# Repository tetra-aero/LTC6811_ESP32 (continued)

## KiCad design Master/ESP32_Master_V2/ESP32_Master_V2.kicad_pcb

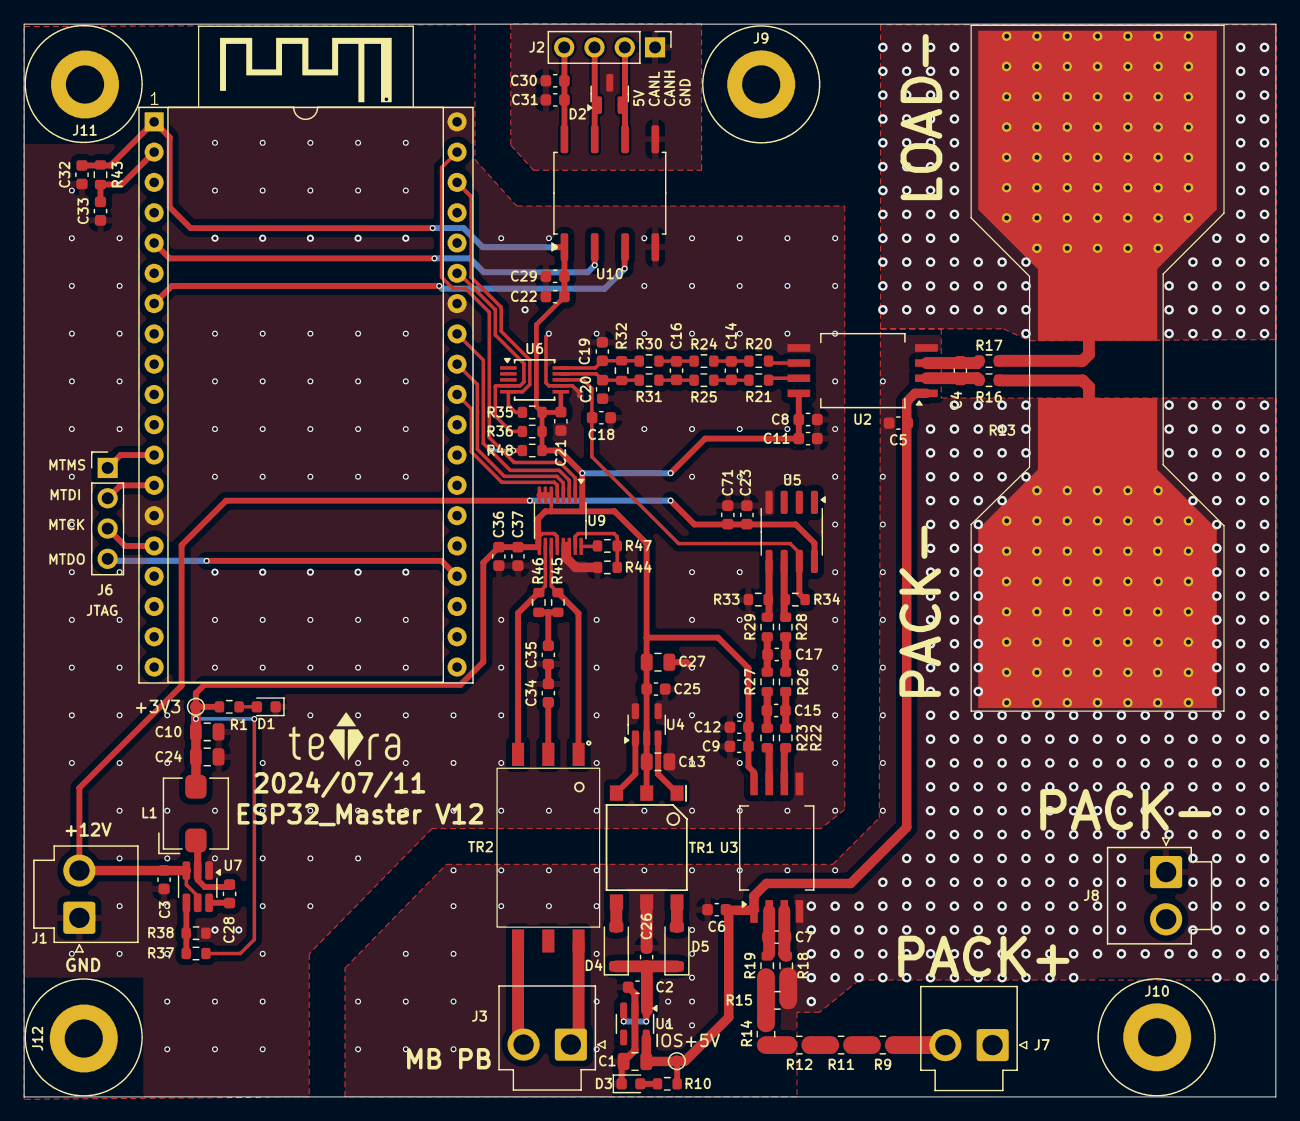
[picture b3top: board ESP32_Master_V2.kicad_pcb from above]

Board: 2 copper layers, 104.9 x 90.0 mm, 106 parts (0 on the bottom side), 67 nets.

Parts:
C1, C10, C13, C24, C27: 10uF/16V; C_0805_2012Metric
C2, C5, C6, C8, C9, C18, C19, C20, C21, C23, C25, C28, C29, C31, C32, C33, C37: 100nF/100V; C_0603_1608Metric
C3, C11, C12: 2.2uF/25V; C_0603_1608Metric
C4, C7: 330pF/100V; C_0603_1608Metric
C14, C15: 2.2nF/16V; C_0603_1608Metric
C16, C17: 220pF/50V; C_0603_1608Metric
C22, C30, C36, C71: 1uF/25V; C_0603_1608Metric
C26: 4.7uF/16V; C_0603_1608Metric
C34, C35: 10nF/100V; C_0603_1608Metric
D1, D3: LED Red; LED_0603_1608Metric
D2: ESD24VS2U; SOT-23
D4, D5: MBR0520; D_SOD-123
J1: PB MB; JST_VH_B2P-VH-B_1x02_P3.96mm_Vertical
J2: CAN; PinHeader_1x04_P2.54mm_Vertical
J3: PA MA; JST_VH_B2P-VH-B_1x02_P3.96mm_Vertical
J6: JTAG /NC; PinHeader_1x04_P2.54mm_Vertical
J7, J8: Check_Votage; JST_VH_B2P-VH-B_1x02_P3.96mm_Vertical
J9, J10, J11, J12: Hole /NC; MountingHole_3.2mm_M3_ISO7380_Pad
L1: 3.3uH; L_Bourns_SRP5030T
LOGO1: teTra /NC; teTra-LOGO
R1, R10: 470R; R_0603_1608Metric
R9, R11, R12, R14: 470KΩ ±0.1% 250mW; R_0805_2012Metric
R13: 0.1MR 1% 15W; R_PSR500HTQFB0L10_Metric_Pad5.2x8.75mm_Hole
R15: 1KΩ ±0.1% 250mW; R_0805_2012Metric
R16, R17, R18, R24, R25, R26, R27, R32: 1K; R_0603_1608Metric
R19: 10R; R_0603_1608Metric
R20, R21, R22, R23: 100R; R_0603_1608Metric
R28, R29: 5.6K; R_0603_1608Metric
R30, R31: 3.3K; R_0603_1608Metric
R33, R34: 33K; R_0603_1608Metric
R35, R36: 4.7K; R_0603_1608Metric
R37: 100K; R_0603_1608Metric
R38: 22.1K; R_0603_1608Metric
R43: 10K; R_0603_1608Metric
R44: 806R; R_0603_1608Metric
R45, R46: 51R; R_0603_1608Metric
R47: 1.2K; R_0603_1608Metric
R48: 2K; R_0603_1608Metric
TP1: IOS+5V; TestPoint_Pad_D1.0mm
TP2: +3V3; TestPoint_Pad_D1.0mm
TR1: Transformer; WURTH-760390015
TR2: HM2108NL
U1: TPS76350; SOT-23-5
U2: AMC1301 or AMC1302; SSO-8_6.8x5.9mm_P1.27mm_Clearance8mm
U3: AMC1301; SSO-8_6.8x5.9mm_P1.27mm_Clearance8mm
U4: SN6501DBV; SOT-23-5
U5: OPA2197IDR; SOIC-8_3.9x4.9mm_P1.27mm
U6: ISL28022; MSOP-10_3x3mm_P0.5mm
U7: LMR51420XDDCR; SOT-23-6_Handsoldering
U8: ESP32-DevKitC V4; ESP32-DevKitc V4_DIP-38_27.9mm×48.2mm
U9: LTC6820; MSOP-16_3x4mm_P0.5mm
U10: ISO1050DUBR; SOP-8_6.62x9.15mm_P2.54mm

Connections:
+3V3: C8.1, C9.1, C10.1, C11.1, C12.1, C13.1, C21.2, C22.1, C24.1, C25.1, C27.1, C29.1, C32.2, C36.2, C37.1, L1.2, R1.2, R35.1, R36.1, R37.2, R43.1, R48.1, TP2.1, TR1.2, U2.8 (VDD2), U3.8 (VDD2), U4.2 (VCC), U6.6 (Vs), U8.1 (3V3), U9.1 (EN), U9.6 (Vcc0), U9.7 (POL), U9.8 (PHA), U9.9 (VCC), U9.12 (MSTR), U10.1 (Vcc1)
+12V: C3.1, C23.1, C71.2, J1.2, U5.8 (V+), U7.3 (VIN), U7.5 (EN)
/CAN/5V_CAN: C30.1, C31.2, J2.4, U10.8 (Vcc2)
/CAN/CANH: D2.2 (K), J2.2, U10.6 (CANL)
/CAN/CANL: D2.1 (K), J2.3, U10.7 (CANH)
/CAN/CAN_GND: C30.2, C31.1, D2.3 (A), J2.1, U10.5 (GND2)
/CAN/CAN_RX: U8.5 (IO34), U10.2 (RXD)
/CAN/CAN_TX: U8.7 (IO32), U10.3 (TXD)
/MA: J3.2, TR2.6
/MCU/IM: R46.1, TR2.3, U9.10 (IM)
/MCU/IP: R45.2, TR2.1, U9.11 (IP)
/MCU/MISO: R48.2, U8.31 (IO19), U9.3 (MISO)
/MCU/MOSI: U8.37 (IO23), U9.2 (MOSI)
/MCU/MTCK: J6.3, U8.15 (IO13)
/MCU/MTDI: J6.2, U8.13 (IO12)
/MCU/MTDO: J6.4, U8.23 (IO15)
/MCU/MTMS: J6.1, U8.12 (IO14)
/MCU/NRST: C33.2, R43.2, U8.2 (EN)
/MCU/SCK: U8.30 (IO18), U9.4 (SCK)
/MCU/SCL: R35.2, U6.5 (SCL), U8.36 (IO22)
/MCU/SDA: R36.2, U6.4 (SDA), U8.33 (IO21)
/MCU/SS: U8.29 (IO5), U9.5 (CSB)
/PA: J3.1, TR2.4
/PowerMonitor/BAT+: J7.2, R9.1
/PowerMonitor/INN: R13.2, R17.1
/PowerMonitor/ISO+5V: C1.1, C5.1, C6.1, R10.2, TP1.1, U1.5 (VOUT), U2.1 (VDD1), U3.1 (VDD1)
/PowerMonitor/VBAT_SENSE: C18.2, R34.2, U5.7, U6.8 (Vbus)
/PowerMonitor/Vin+: C19.2, R30.1, R32.1, U6.10 (Vin+)
/PowerMonitor/Vin-: C20.2, R31.1, R32.2, U6.9 (Vin-)
GND: C3.2, C8.2, C9.2, C10.2, C11.2, C12.2, C13.2, C18.1, C19.1, C20.1, C21.1, C22.2, C23.2, C24.2, C25.2, C27.2, C29.2, C32.1, C33.1, C34.2, C35.1, C36.1, C37.2, C71.1, D1.1 (K), J1.1, R33.2, R38.2, R44.2, U2.5 (GND2), U3.5 (GND2), U4.4 (GND), U4.5 (GND), U5.4 (V-), U6.7 (GND), U7.1 (GND), U8.14 (GND), U8.32 (GND), U8.38 (GND), U9.13 (SLOW), U9.14 (GND), U10.4 (GND1)
GNDA: C1.2, C2.2, C5.2, C6.2, C26.2, D3.1 (K), J8.1, R13.1, R15.2, R16.1, R18.2, TR1.5, U1.2 (GND), U2.4 (GND1), U3.4 (GND1)
unnamed: C14.1, R20.1, R24.1
unnamed: C14.2, R21.1, R25.1
unnamed: C15.1, R22.1, R26.1
unnamed: C15.2, R23.1, R27.1
unnamed: C16.1, R24.2, R30.2
unnamed: C16.2, R25.2, R31.2
unnamed: C17.1, R26.2, R28.1
unnamed: C17.2, R27.2, R29.1
unnamed: C34.1, TR2.2
unnamed: C35.2, R45.1, R46.2
unnamed: D1.2 (A), R1.1
unnamed: D3.2 (A), R10.1
unnamed: D4.2 (A), TR1.4
unnamed: C2.1, C26.1, D4.1 (K), D5.1 (K), U1.1 (VIN), U1.3 (EN)
unnamed: D5.2 (A), TR1.6
unnamed: R9.2, R11.1
unnamed: R11.2, R12.1
unnamed: R12.2, R14.1
unnamed: R14.2, R15.1, R19.1
unnamed: C4.2, R17.2, U2.3 (VINN)
unnamed: C4.1, R16.2, U2.2 (VINP)
unnamed: R20.2, U2.6 (VOUTN)
unnamed: R21.2, U2.7 (VOUTP)
unnamed: C7.2, R18.1, U3.3 (VINN)
unnamed: C7.1, R19.2, U3.2 (VINP)
unnamed: R22.2, U3.6 (VOUTN)
unnamed: R23.2, U3.7 (VOUTP)
unnamed: TR1.3, U4.1 (D1)
unnamed: TR1.1, U4.3 (D2)
unnamed: R29.2, R33.1, U5.5 (+)
unnamed: R28.2, R34.1, U5.6 (-)
unnamed: C28.2, U7.6 (CB)
unnamed: R37.1, R38.1, U7.4 (FB)
unnamed: C28.1, L1.1, U7.2 (SW)
unnamed: R47.1, U9.16 (IBIAS)
unnamed: R44.1, R47.2, U9.15 (ICMP)

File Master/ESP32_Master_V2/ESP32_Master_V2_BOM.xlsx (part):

ESP32_Master_V2_BOM
Item | Qty | Reference(s) | Value | Footprint | Datasheet | Description | Link | MPN
1 | 5 | C1, C10, C13, C24, C27 | 10uF/16V | Capacitor_SMD:C_0805_2012Metric | https://mm.digikey.com/Volume0/opasdata/d220001/medias/docus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 | 10uF ±10% 16V Ceramic Capacitor X5R 0805 (2012 Metric) | https://www.digikey.jp/en/products/detail/samsung-electro-me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 | CL21A106KOQNNNE
2 | 17 | C2, C5, C6, C8, C9, C18, C19, C20, C21, C23, C25, C28, C29, C31, C32, C33, C37 | 100nF/100V | Capacitor_SMD:C_0603_1608Metric | https://www.digikey.jp/en/products/detail/samsung-electro-me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 | 0.1uF ±10% 100V Ceramic Capacitor X7R 0603 (1608 Metric) | https://www.digikey.jp/en/products/detail/samsung-electro-me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 | CL10B104KC8NNNC
3 | 3 | C3, C11, C12 | 2.2uF/25V | Capacitor_SMD:C_0603_1608Metric | https://search.murata.co.jp/Ceramy/image/img/A01X/G101/ENG/G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 | 2.2uF ±10% 25V Ceramic Capacitor X5R 0603 (1608 Metric) | https://www.digikey.jp/en/products/detail/murata-electronics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 | GRM188R61E225KA12D
4 | 2 | C4, C7 | 330pF/100V | Capacitor_SMD:C_0603_1608Metric | https://search.murata.co.jp/Ceramy/image/img/A01X/G101/ENG/G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 | 330 pF ±10% 100V Ceramic Capacitor X7R 0603 (1608 Metric) | https://www.digikey.jp/en/products/detail/murata-electronics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 | GRM188R72A331KA01D
5 | 2 | C14, C15 | 2.2nF/16V | Capacitor_SMD:C_0603_1608Metric | https://connect.kemet.com:7667/gateway/IntelliData-Component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 | 2200 pF ±10% 16V Ceramic Capacitor X7R 0603 (1608 Metric) | https://www.digikey.jp/en/products/detail/kemet/C0603C222K4R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 | C0603C222K4RECAUTO
6 | 2 | C16, C17 | 220pF/50V | Capacitor_SMD:C_0603_1608Metric | https://search.murata.co.jp/Ceramy/image/img/A01X/G101/ENG/G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 | 220 pF ±5% 50V Ceramic Capacitor C0G, NP0 0603 (1608 Metric) | https://www.digikey.jp/en/products/detail/murata-electronics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 | GCM1885C1H221JA16D
7 | 4 | C22, C30, C36, C71 | 1uF/25V | Capacitor_SMD:C_0603_1608Metric | https://mm.digikey.com/Volume0/opasdata/d220001/medias/docus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 | 1 µF ±10% 25V Ceramic Capacitor X7R 0603 (1608 Metric) | https://www.digikey.jp/en/products/detail/samsung-electro-me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 | CL10B105KA8NNNC
8 | 1 | C26 | 4.7uF/16V | Capacitor_SMD:C_0603_1608Metric | https://mm.digikey.com/Volume0/opasdata/d220001/medias/docus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 | 4.7uF ±10% 16V Ceramic Capacitor X5R 0603 (1608 Metric) | https://www.digikey.jp/en/products/detail/samsung-electro-me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 | CL10A475KO8NNNC
9 | 2 | C34, C35 | 10nF/100V | Capacitor_SMD:C_0603_1608Metric | https://search.murata.co.jp/Ceramy/image/img/A01X/G101/ENG/G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 | 10000 pF ±10% 100V Ceramic Capacitor X7R 0603 (1608 Metric) | https://www.digikey.jp/en/products/detail/murata-electronics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 | GCM188R72A103KA37D
10 | 2 | D1, D3 | LED Red | LED_SMD:LED_0603_1608Metric | https://docs.broadcom.com/doc/AV02-0112EN | Red 626nm LED Indication - Discrete 1.9V 0603 (1608 Metric) | https://www.digikey.jp/en/products/detail/broadcom-limited/H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 | HSMC-C191
11 | 1 | D2 | ESD24VS2U | Package_TO_SOT_SMD:SOT-23 | https://www.infineon.com/dgdl/Infineon-ESD24VS2U-DS-v01_01-e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 | 41V Clamp 5A (8/20us) Ipp Tvs Diode Surface Mount PG-SOT23 | https://www.digikey.jp/en/products/detail/infineon-technolog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 | ESD24VS2UE6327HTSA1
12 | 2 | D4, D5 | MBR0520 | Diode_SMD:D_SOD-123 | http://www.mccsemi.com/up_pdf/MBR0520~MBR0580(SOD123).pdf | Diode 20 V 500mA Surface Mount SOD-123 | https://www.digikey.jp/en/products/detail/micro-commercial-c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 | MBR0520-TP
13 | 4 | J1，J3，J7, J8 | JST_VH_B2P | Connector_JST:JST_VH_B2P-VH-B_1x02_P3.96mm_Vertical | https://www.jst-mfg.com/product/pdf/eng/eVH.pdf | Connector Header Through Hole 2 position 0.156" (3.96mm) | https://www.digikey.jp/en/products/detail/jst-sales-america-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 | B2P-VH
14 | 2 | J2，J6 | JTAG /NC | Connector_PinHeader_2.54mm:PinHeader_1x04_P2.54mm_Vertical | https://cdn.amphenol-cs.com/media/wysiwyg/files/drawing/g800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 | Connector Header Through Hole 4 position 0.100" (2.54mm) | https://www.digikey.jp/en/products/detail/amphenol-cs-commer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 | G800W304018EU
15 | 1 | L1 | 3.3uH | Inductor_SMD:L_Bourns_SRP5030T | https://www.bourns.com/docs/Product-Datasheets/SRP5030CC.pdf | 3.3uH Shielded Wirewound Inductor 5 A 38mOhm Max Nonstandard | https://www.digikey.jp/en/products/detail/bourns-inc/SRP5030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 | SRP5030CC-3R3M
16 | 2 | R1, R10 | 470R | Resistor_SMD:R_0603_1608Metric | https://www.yageo.com/upload/media/product/products/datashee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 | 470 Ohms ±5% 0.1W, 1/10W Chip Resistor 0603 (1608 Metric) Moisture Resistant Th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 | https://www.digikey.jp/en/products/detail/yageo/RC0603JR-074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 | RC0603JR-07470RL
17 | 4 | R9, R11, R12, R14 | 470KΩ ±0.1% 250mW | Resistor_SMD:R_0805_2012Metric | https://industrial.panasonic.com/cdbs/www-data/pdf/RDM0000/A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 | 470 kOhms ±0.1% 0.25W, 1/4W Chip Resistor 0805 (2012 Metric) Automotive AEC-Q20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 | https://www.digikey.jp/en/products/detail/panasonic-electron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 | ERJ-PB6B4703V
18 | 1 | R13 | 100uOhm 1% 15W | Resistor_SMD:R_PSR500HTQFB0L10_Metric_Pad5.2x8.75mm_Hole | https://fscdn.rohm.com/en/products/databook/datasheet/passiv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 | 100uOhms ±1% 15W Chip Resistor Nonstandard Automotive AEC-Q200, Current Sense M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 | https://www.digikey.jp/en/products/detail/rohm-semiconductor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 | PSR500HTQFB0L10
19 | 1 | R15 | 1KΩ ±0.1% 250mW | Resistor_SMD:R_0805_2012Metric | https://industrial.panasonic.com/cdbs/www-data/pdf/RDM0000/A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 | 1 kOhms ±0.1% 0.25W, 1/4W Chip Resistor 0805 (2012 Metric) Automotive AEC-Q200,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 | https://www.digikey.jp/en/products/detail/panasonic-electron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 | ERJ-PB6B1001V
20 | 8 | R16, R17, R18, R24, R25, R26, R27, R32 | 1K | Resistor_SMD:R_0603_1608Metric | https://www.vishay.com/docs/20035/dcrcwe3.pdf | 1 kOhms ±1% 0.1W, 1/10W Chip Resistor 0603 (1608 Metric) Automotive AEC-Q200 Th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 | https://www.digikey.jp/en/products/detail/vishay-dale/CRCW06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 | CRCW06031K00FKEA
21 | 1 | R19 | 10R | Resistor_SMD:R_0603_1608Metric | https://www.yageo.com/upload/media/product/app/datasheet/rch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 | 10 Ohms ±5% 0.1W, 1/10W Chip Resistor 0603 (1608 Metric) Moisture Resistant Thi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 | https://www.digikey.jp/en/products/detail/yageo/RC0603JR-071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 | RC0603JR-0710RL
22 | 4 | R20, R21, R22, R23 | 100R | Resistor_SMD:R_0603_1608Metric | https://www.yageo.com/upload/media/product/app/datasheet/rch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 | 100 Ohms ±1% 0.1W, 1/10W Chip Resistor 0603 (1608 Metric) Moisture Resistant Th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 | https://www.digikey.jp/en/products/detail/yageo/RC0603FR-071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 | RC0603FR-07100RL
23 | 2 | R28, R29 | 5.6K | Resistor_SMD:R_0603_1608Metric | https://www.yageo.com/upload/media/product/productsearch/dat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 | 5.6 kOhms ±5% 0.1W, 1/10W Chip Resistor 0603 (1608 Metric) Moisture Resistant T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 | https://www.digikey.jp/en/products/detail/yageo/RC0603JR-075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 | RC0603JR-075K6L
24 | 2 | R30, R31 | 3.3K | Resistor_SMD:R_0603_1608Metric | https://www.yageo.com/upload/media/product/app/datasheet/rch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 | 3.3 kOhms ±1% 0.1W, 1/10W Chip Resistor 0603 (1608 Metric) Moisture Resistant T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 | https://www.digikey.jp/en/products/detail/yageo/RC0603FR-073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 | RC0603FR-073K3L
25 | 2 | R33, R34 | 33K | Resistor_SMD:R_0603_1608Metric | https://www.yageo.com/upload/media/product/productsearch/dat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 | 33 kOhms ±1% 0.1W, 1/10W Chip Resistor 0603 (1608 Metric) Automotive AEC-Q200, 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 | https://www.digikey.jp/en/products/detail/yageo/AC0603FR-073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 | AC0603FR-0733KL
26 | 2 | R35, R36 | 4.7K | Resistor_SMD:R_0603_1608Metric | https://www.yageo.com/upload/media/product/products/datashee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 | 4.7 kOhms ±5% 0.1W, 1/10W Chip Resistor 0603 (1608 Metric) Moisture Resistant T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 | https://www.digikey.jp/en/products/detail/yageo/RC0603JR-074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 | RC0603JR-074K7L
27 | 1 | R37 | 100K | Resistor_SMD:R_0603_1608Metric | https://www.yageo.com/upload/media/product/app/datasheet/rch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 | 100 kOhms ±5% 0.1W, 1/10W Chip Resistor 0603 (1608 Metric) Moisture Resistant T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 | https://www.digikey.jp/en/products/detail/yageo/RC0603JR-071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 | RC0603JR-07100KL
28 | 1 | R38 | 22.1K | Resistor_SMD:R_0603_1608Metric | https://www.seielect.com/catalog/sei-rmcf_rmcp.pdf | 22.1 kOhms ±1% 0.1W, 1/10W Chip Resistor 0603 (1608 Metric) Automotive AEC-Q200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 | https://www.digikey.jp/en/products/detail/stackpole-electron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 | RMCF0603FT22K1
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
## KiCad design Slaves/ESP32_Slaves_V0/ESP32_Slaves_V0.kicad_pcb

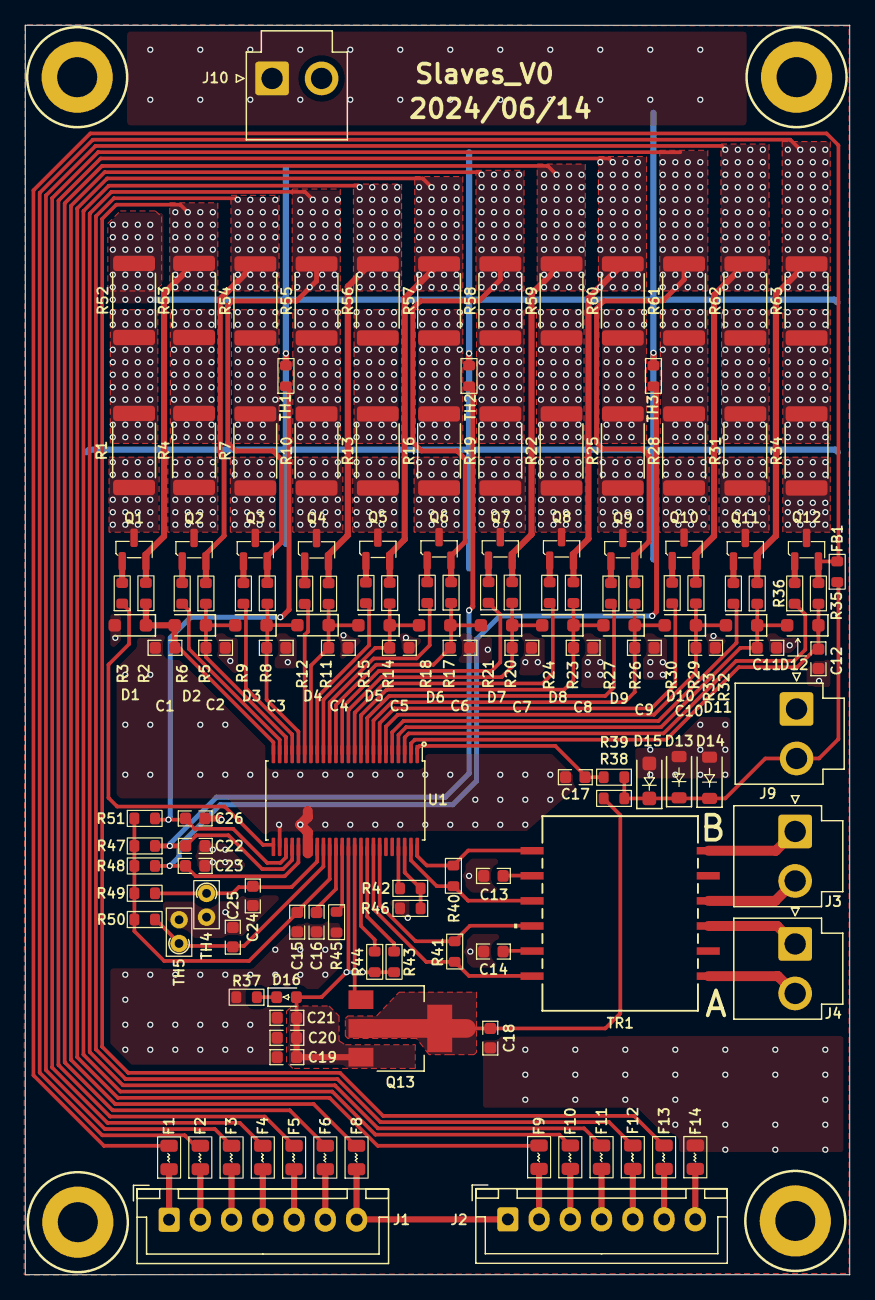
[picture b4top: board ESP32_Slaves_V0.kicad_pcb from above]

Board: 2 copper layers, 65.9 x 99.9 mm, 150 parts (1 on the bottom side), 114 nets.

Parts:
C1, C2, C3, C4, C5, C6, C7, C8, C9, C10, C11, C12, C17, C18, C22, C23, C24, C25, C26: 100nF 100V; C_0603_1608Metric
C13, C14: 100pF 100V; C_0603_1608Metric
C15, C16, C19, C20, C21: 1uF 25V; C_0603_1608Metric
D1, D2, D3, D4, D5, D6, D7, D8, D9, D10, D11, D12: PDZ7.5B; D_SOD-323_HandSoldering
D13, D14: 1N4148W; D_SOD-123
D15: BZT52H-C62; D_SOD-123F
D16: LED Red; LED_0603_1608Metric
F1, F2, F3, F4, F5, F6, F8, F9, F10, F11, F12, F13, F14: MPZ2012S102ATD25; Fuse_0805_2012Metric
FB1: BLM18PG330SN1D; R_0603_1608Metric
J1, J2: B7B-XH-A; JST_XH_B7B-XH-A_1x07_P2.50mm_Vertical_BAT_6S
J3: PB MB; JST_VH_B2P-VH-B_1x02_P3.96mm_Vertical
J4: PB MA; JST_VH_B2P-VH-B_1x02_P3.96mm_Vertical
J5, J6, J7, J8: Hole /NC; MountingHole_3.2mm_M3_ISO7380_Pad
J9: BAT+; JST_VH_B2P-VH-B_1x02_P3.96mm_Vertical
J10: PACK-; JST_VH_B2P-VH-B_1x02_P3.96mm_Vertical
LOGO1: teTra; teTra-LOGO
Q1, Q2, Q3, Q4, Q5, Q6, Q7, Q8, Q9, Q10, Q11, Q12: TSM2323; SOT-23
Q13: NSV1C201MZ4; SOT-223
R1, R4, R7, R10, R13, R16, R19, R22, R25, R28, R31, R34, R52, R53, R54, R55, R56, R57, R58, R59, R60, R61, R62, R63: 18R 1W 2512; R_2512_6332Metric
R2, R5, R8, R11, R14, R17, R20, R23, R26, R29, R32, R35, R38, R39, R40, R41: 100R; R_0603_1608Metric
R3, R6, R9, R12, R15, R18, R21, R24, R27, R30, R33, R36: 3.3K; R_0603_1608Metric
R37, R42: 1.2K; R_0603_1608Metric
R43, R45: 0; R_0603_1608Metric
R44: 1M; R_0603_1608Metric
R46: 806R; R_0603_1608Metric
R47, R48, R49, R50, R51: 10K; R_0603_1608Metric
TH1, TH2, TH3: 10K NTC; R_0603_1608Metric
TH4, TH5: 10K NTC; R_Axial_DIN0204_L3.6mm_D1.6mm_P1.90mm_Vertical
TR1: HM2102NL; HM2102NL_PUL
U1: LTC6811HG-1; TSSOP-48_6.1x12.5mm_P0.5mm

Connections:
/BAT+: D13.1 (K), D14.1 (K), D15.1 (K), FB1.1, J9.2, R38.1, R39.1
/C1: F13.1, J2.1 (Pin_2)
/C1_G: F14.1, J2.0 (Pin_1)
/C2: F12.1, J2.2 (Pin_3)
/C2_G: F8.1, J1.0 (Pin_1), J2.6 (Pin_7)
/C3: F11.1, J2.3 (Pin_4)
/C4: F10.1, J2.4 (Pin_5)
/C5: F9.1, J2.5 (Pin_6)
/C7: F6.1, J1.1 (Pin_2)
/C8: F5.1, J1.2 (Pin_3)
/C9: F4.1, J1.3 (Pin_4)
/C10: F3.1, J1.4 (Pin_5)
/C11: F2.1, J1.5 (Pin_6)
/C12: F1.1, J1.6 (Pin_7)
/DRIVE: Q13.1 (B), U1.38 (DRIVE)
/IMA: R41.2, TR1.12, U1.41 (IMA)
/IMB: R40.2, TR1.9, U1.47 (IMB)
/IPA: R41.1, TR1.10, U1.42 (IPA)
/IPB: R40.1, TR1.7, U1.48 (IPB)
/T1: C26.1, R51.2, TH1.1, U1.27 (GPIO1)
/T2: C22.1, R47.1, TH2.1, U1.28 (GPIO2)
/T3: C23.1, R48.1, TH3.1, U1.29 (GPIO3)
/T4: C24.1, R49.1, TH4.1, U1.32 (GPIO4)
/T5: C25.1, R50.1, TH5.1, U1.33 (GPIO5)
/Vref2: C15.1, R47.2, R48.2, R49.2, R50.2, R51.1, U1.34 (Vref2)
/Vreg: C19.1, C20.1, C21.1, D16.2 (A), Q13.3 (E), R43.2, R44.2, U1.37 (Vreg)
/cell1/C: C1.1, D1.1 (K), D2.2 (A), R2.1, U1.24 (C1)
/cell1/C+: F13.2, Q1.2 (S), R2.2, R53.1
/cell1/S: R3.1, U1.25 (S1)
/cell2/C: C2.1, D2.1 (K), D3.2 (A), R5.1, U1.22 (C2)
/cell2/C+: F12.2, Q2.2 (S), R5.2, R54.1
/cell2/S: R6.1, U1.23 (S2)
/cell3/C: C3.1, D3.1 (K), D4.2 (A), R8.1, U1.20 (C3)
/cell3/C+: F11.2, Q3.2 (S), R8.2, R55.1
/cell3/S: R9.1, U1.21 (S3)
/cell4/C: C4.1, D4.1 (K), D5.2 (A), R11.1, U1.18 (C4)
/cell4/C+: F10.2, Q4.2 (S), R11.2, R56.1
/cell4/S: R12.1, U1.19 (S4)
/cell5/C: C5.1, D5.1 (K), D6.2 (A), R14.1, U1.16 (C5)
/cell5/C+: F9.2, Q5.2 (S), R14.2, R57.1
/cell5/S: R15.1, U1.17 (S5)
/cell6/C: C6.1, D6.1 (K), D7.2 (A), R17.1, U1.14 (C6)
/cell6/C+: F8.2, Q6.2 (S), R17.2, R58.1
/cell6/S: R18.1, U1.15 (S6)
/cell7/C: C7.1, D7.1 (K), D8.2 (A), R20.1, U1.12 (C7)
/cell7/C+: F6.2, Q7.2 (S), R20.2, R59.1
/cell7/S: R21.1, U1.13 (S7)
/cell8/C: C8.1, D8.1 (K), D9.2 (A), R23.1, U1.10 (C8)
/cell8/C+: F5.2, Q8.2 (S), R23.2, R60.1
/cell8/S: R24.1, U1.11 (S8)
/cell9/S: R27.1, U1.9 (S9)
/cell10/C: C10.1, D10.1 (K), D11.2 (A), R29.1, U1.6 (C10)
/cell10/C+: F3.2, Q10.2 (S), R29.2, R62.1
/cell10/C-: F4.2, Q9.2 (S), R26.2, R61.1
/cell10/CM: C9.1, D9.1 (K), D10.2 (A), R26.1, U1.8 (C9)
/cell10/S: R30.1, U1.7 (S10)
/cell11/C: C11.1, D11.1 (K), D12.2 (A), R32.1, U1.4 (C11)
/cell11/C+: F2.2, Q11.2 (S), R32.2, R63.1
/cell11/S: R33.1, U1.5 (S11)
/cell12/C: C12.1, D12.1 (K), R35.1, U1.2 (C12)
/cell12/C+: F1.2, FB1.2, Q12.2 (S), R35.2
/cell12/S: R36.1, U1.3 (S12)
GND_PACK: C1.2, C2.2, C3.2, C4.2, C5.2, C6.2, C7.2, C8.2, C9.2, C10.2, C11.2, C12.2, C13.2, C14.2, C15.2, C16.2, C17.2, C18.2, C19.2, C20.2, C21.2, C22.2, C23.2, C24.2, C25.2, C26.2, D1.2 (A), D13.2 (A), D14.2 (A), D15.2 (A), F14.2, J10.1, R37.2, R45.2, R46.2, R52.1, TH1.2, TH2.2, TH3.2, TH4.2, TH5.2, U1.26 (C0), U1.30 (V-**), U1.31 (V-)
unnamed: C13.1, TR1.8
unnamed: C14.1, TR1.11
unnamed: C18.1, Q13.2 (C), Q13.4 (C), R38.2
unnamed: D16.1 (K), R37.1
unnamed: J3.1, TR1.6
unnamed: J3.2, TR1.4
unnamed: J4.1, TR1.3
unnamed: J4.2, TR1.1
unnamed: Q1.3 (D), R1.2
unnamed: Q1.1 (G), R3.2
unnamed: Q2.3 (D), R4.2
unnamed: Q2.1 (G), R6.2
unnamed: Q3.3 (D), R7.2
unnamed: Q3.1 (G), R9.2
unnamed: Q4.3 (D), R10.2
unnamed: Q4.1 (G), R12.2
unnamed: Q5.3 (D), R13.2
unnamed: Q5.1 (G), R15.2
unnamed: Q6.3 (D), R16.2
unnamed: Q6.1 (G), R18.2
unnamed: Q7.3 (D), R19.2
unnamed: Q7.1 (G), R21.2
unnamed: Q8.3 (D), R22.2
unnamed: Q8.1 (G), R24.2
unnamed: Q9.3 (D), R25.2
unnamed: Q9.1 (G), R27.2
unnamed: Q10.3 (D), R28.2
unnamed: Q10.1 (G), R30.2
unnamed: Q11.3 (D), R31.2
unnamed: Q11.1 (G), R33.2
unnamed: Q12.3 (D), R34.2
unnamed: Q12.1 (G), R36.2
unnamed: R1.1, R52.2
unnamed: R4.1, R53.2
unnamed: R10.1, R55.2
unnamed: R13.1, R56.2
unnamed: R16.1, R57.2
unnamed: R19.1, R58.2
unnamed: R22.1, R59.2
unnamed: R25.1, R60.2
unnamed: R28.1, R61.2
unnamed: R31.1, R62.2
unnamed: R34.1, R63.2
unnamed: R7.1, R54.2
unnamed: R45.1, U1.36 (DTEN)
unnamed: R42.1, U1.45 (IBIAS)
unnamed: R42.2, R46.1, U1.46 (ICMP)
unnamed: R43.1, U1.40 (ISOMD)
unnamed: C17.1, R39.2, U1.1 (V+)
unnamed: C16.1, U1.35 (Vref1)
unnamed: R44.1, U1.39 (WDT)

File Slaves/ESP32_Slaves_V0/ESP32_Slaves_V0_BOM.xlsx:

NO. | Reference | Value | Footprint | Datasheet | Description | Link | MPN | Quality
1 | C1-C12, C17, C18, C22-C26 | 100nF 100V | Library:C_0603_1608Metric | https://www.digikey.jp/en/products/detail/samsung-electro-me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 | 0.1 uF ±10% 100V Ceramic Capacitor X7R 0603 (1608 Metric) | https://www.digikey.jp/en/products/detail/samsung-electro-me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 | CL10B104KC8NNNC | 19
2 | C13, C14 | 100pF 100V | Library:C_0603_1608Metric | https://www.yageo.com/upload/media/product/app/datasheet/mlc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 | 100 pF ±10% 100V Ceramic Capacitor X7R 0603 (1608 Metric) | https://www.digikey.jp/en/products/detail/yageo/CC0603KRX7R0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 | CC0603KRX7R0BB101 | 2
3 | C15, C16, C19-C21 | 1uF/25V | Library::C_0603_1608Metric | https://mm.digikey.com/Volume0/opasdata/d220001/medias/docus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 | 1 µF ±10% 25V Ceramic Capacitor X7R 0603 (1608 Metric) | https://www.digikey.jp/en/products/detail/samsung-electro-me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 | CL10B105KA8NNNC | 5
4 | D1-D12 | PDZ7.5B | Library:D_SOD-323_HandSoldering | https://assets.nexperia.com/documents/data-sheet/PDZ-B_SER.pdf | Zener Diode 7.6 V 400 mW ±2% Surface Mount SOD-323 | https://www.digikey.jp/en/products/detail/nexperia-usa-inc/P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 | PDZ7.5BZ | 12
5 | D13, D14 | 1N4148W | Library:D_SOD-123 | https://www.diodes.com/assets/Datasheets/BAV16W_1N4148W.pdf | Diode 100 V 300mA Surface Mount SOD-123 | https://www.digikey.jp/en/products/detail/diodes-incorporate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 | 1N4148W-7-F | 2
6 | D15 | BZT52H-C62 | Library:D_SOD-123F | https://assets.nexperia.com/documents/data-sheet/BZT52H_SER.pdf | Zener Diode 62 V 375 mW ±5% Surface Mount SOD-123F | https://www.digikey.jp/en/products/detail/nexperia-usa-inc/B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 | BZT52H-C62,115 | 1
7 | D16 | LED Red | Library:LED_0603_1608Metric | https://optoelectronics.liteon.com/upload/download/DS-22-99-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 | Red 631nm LED Indication - Discrete 2V 0603 (1608 Metric) | https://www.digikey.jp/en/products/detail/liteon/LTST-C190KR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 | LTST-C190KRKT | 1
8 | F1-F6, F8-F14 | MPZ2012S102ATD25 | Library:Fuse_0805_2012Metric | https://product.tdk.com/en/system/files?file=dam/doc/product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 | 1 kOhms @ 100 MHz 1 Power Line Ferrite Bead 0805 (2012 Metric) 1.5A 150mOhm | https://www.digikey.jp/en/products/detail/tdk-corporation/MP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 | MPZ2012S102ATD25 | 13
9 | FB1 | BLM18PG330SN1D | Library:R_0603_1608Metric | https://www.murata.com/en-us/products/productdata/8796738650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 | 33 Ohms @ 100 MHz 1 Power Line Ferrite Bead 0603 (1608 Metric) 3A 25mOhm | https://www.digikey.jp/en/products/detail/murata-electronics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 | BLM18PG330SN1D | 1
10 | J1, J2 | B7B-XH-A | Library:JST_XH_B7B-XH-A_1x07_P2.50mm_Vertical_BAT_6S | https://www.jst-mfg.com/product/pdf/eng/eXH.pdf | Connector Header Through Hole 7 position 0.098" (2.50mm) | https://www.digikey.jp/en/products/detail/jst-sales-america-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 | B7B-XH-A | 2
11 | J3 | PB MB | Library:JST_VH_B2P-VH-B_1x02_P3.96mm_Vertical | https://tools.molex.com/pdm_docs/sd/705430001_sd.pdf | Connector Header Through Hole 2 position 0.100" (2.54mm) | https://www.digikey.jp/en/products/detail/molex/0705430001/1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 | 70543-0001 | 1
12 | J4 | PB MA | Library:JST_VH_B2P-VH-B_1x02_P3.96mm_Vertical | https://tools.molex.com/pdm_docs/sd/705430001_sd.pdf | Connector Header Through Hole 2 position 0.100" (2.54mm) | https://www.digikey.jp/en/products/detail/molex/0705430001/1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 | 70543-0001 | 1
13 | J9 | BAT+ | Library:JST_VH_B2P-VH-B_1x02_P3.96mm_Vertical | https://www.jst-mfg.com/product/pdf/eng/eVH.pdf | Connector Header Through Hole 2 position 0.156" (3.96mm) | https://www.digikey.jp/en/products/detail/jst-sales-america-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 | B2P-VH | 1
14 | J10 | PACK- | Library:JST_VH_B2P-VH-B_1x02_P3.96mm_Vertical | https://www.jst-mfg.com/product/pdf/eng/eVH.pdf | Connector Header Through Hole 2 position 0.156" (3.96mm) | https://www.digikey.jp/en/products/detail/jst-sales-america-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 | B2P-VH | 1
15 | Q1-Q12 | TSM2323 | Library:SOT-23 | https://www.taiwansemi.com/assets/uploads/datasheet/TSM2323_F15.pdf | P-Channel 20 V 4.7A (Ta) 1.25W (Ta) Surface Mount SOT-23 | https://www.digikey.jp/en/products/detail/taiwan-semiconduct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 | TSM2323CX RFG | 12
16 | Q13 | NSV1C201MZ4 | Library:SOT-223 | https://www.onsemi.com/pdf/datasheet/nss1c201mz4-d.pdf | Bipolar (BJT) Transistor NPN 100 V 2 A 100MHz 800 mW Surface Mount SOT-223 (TO-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 | https://www.digikey.jp/en/products/detail/onsemi/NSV1C201MZ4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 | NSV1C201MZ4T1G | 1
17 | R1, R4, R7, R10, R13, R16, R19, R22, R25, R28, R31, R34, R52-R63 | 18R 1W 2512 | Library:R_2512_6332Metric | https://www.te.com/commerce/DocumentDelivery/DDEController?A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 | 18 Ohms ±1% 2W Chip Resistor 2512 (6432 Metric) Automotive AEC-Q200 Thick Film | https://www.digikey.jp/en/products/detail/te-connectivity-pa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 | 352118RFT | 24
18 | R2, R5, R8, R11, R14, R17, R20, R23, R26, R29, R32, R35, R38-R41 | 100R | Library:R_0603_1608Metric | https://www.yageo.com/upload/media/product/app/datasheet/rch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 | 100 Ohms ±1% 0.1W, 1/10W Chip Resistor 0603 (1608 Metric) Moisture Resistant Th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 | https://www.digikey.jp/en/products/detail/yageo/RC0603FR-071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 | RC0603FR-07100RL | 16
19 | R3, R6, R9, R12, R15, R18, R21, R24, R27, R30, R33, R36 | 3.3K | Library:R_0603_1608Metric | https://www.yageo.com/upload/media/product/app/datasheet/rch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 | 3.3 kOhms ±1% 0.1W, 1/10W Chip Resistor 0603 (1608 Metric) Moisture Resistant T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 | https://www.digikey.jp/en/products/detail/yageo/RC0603FR-073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 | RC0603FR-073K3L | 12
20 | R37, R42 | 1.2K | Library:R_0603_1608Metric | https://www.yageo.com/upload/media/product/productsearch/dat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 | 1.2 kOhms ±5% 0.1W, 1/10W Chip Resistor 0603 (1608 Metric) Moisture Resistant T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 | https://www.digikey.jp/en/products/detail/yageo/RC0603JR-071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 | RC0603JR-071K2L | 2
21 | R43, R45 | 0 | Library:R_0603_1608Metric | https://www.yageo.com/upload/media/product/productsearch/dat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 | 0 Ohms Jumper Chip Resistor 0603 (1608 Metric) Moisture Resistant Thick Film | https://www.digikey.jp/en/products/detail/yageo/RC0603JR-070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 | RC0603JR-070RL | 2
22 | R44 | 1M | Library:R_0603_1608Metric | https://www.yageo.com/upload/media/product/app/datasheet/rch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 | 1 MOhms ±5% 0.1W, 1/10W Chip Resistor 0603 (1608 Metric) Moisture Resistant Thi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 | https://www.digikey.jp/en/products/detail/yageo/RC0603JR-071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 | RC0603JR-071ML | 1
23 | R46 | 806R | Library:R_0603_1608Metric | https://www.yageo.com/upload/media/product/app/datasheet/rch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 | 806 Ohms ±1% 0.1W, 1/10W Chip Resistor 0603 (1608 Metric) Moisture Resistant Th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 | https://www.digikey.jp/en/products/detail/yageo/RC0603FR-078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 | RC0603FR-07806RL | 1
24 | R47-R51 | 10K | Library:R_0603_1608Metric | https://www.seielect.com/catalog/sei-rmcf_rmcp.pdf | 10 kOhms ±5% 0.1W, 1/10W Chip Resistor 0603 (1608 Metric) Automotive AEC-Q200 T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 | https://www.digikey.jp/en/products/detail/stackpole-electron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 | RMCF0603JT10K0 | 5
25 | TH1-TH3 | 10K NTC | Library:R_0603_1608Metric | https://www.murata.com/en-us/api/pdfdownloadapi?cate=luNTCfo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 | THERMISTOR NTC 10KOHM 3380K 0603 | https://www.digikey.jp/en/products/detail/murata-electronics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 | NCU18XH103F6SRB | 3
26 | TH4, TH5 | 10K NTC | Library:R_Axial_DIN0204_L3.6mm_D1.6mm_P1.90mm_Vertical | https://www.cantherm.com/wp-content/uploads/2017/05/cantherm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 | THERMISTOR NTC 10KOHM 3380K BEAD | https://www.digikey.jp/en/products/detail/cantherm/MF52C1103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 | MF52C1103F3380 | 2
27 | TR1 | HM2102NLT | Library:HM2102NL_PUL | https://productfinder.pulseelectronics.com/api/open/part-att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 | 150µH Pulse Transformer 1:1 Surface Mount | https://www.digikey.jp/en/products/detail/pulse-electronics/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 | HM2102NLT | 1
28 | U1 | LTC6811HG-1 | Library:TSSOP-48_6.1x12.5mm_P0.5mm | https://www.analog.com/media/en/technical-documentation/data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 | Battery Battery Monitor IC Multi-Chemistry 48-SSOP | https://www.digikey.jp/en/products/detail/analog-devices-inc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 | LTC6811HG-1#3ZZPBF | 1

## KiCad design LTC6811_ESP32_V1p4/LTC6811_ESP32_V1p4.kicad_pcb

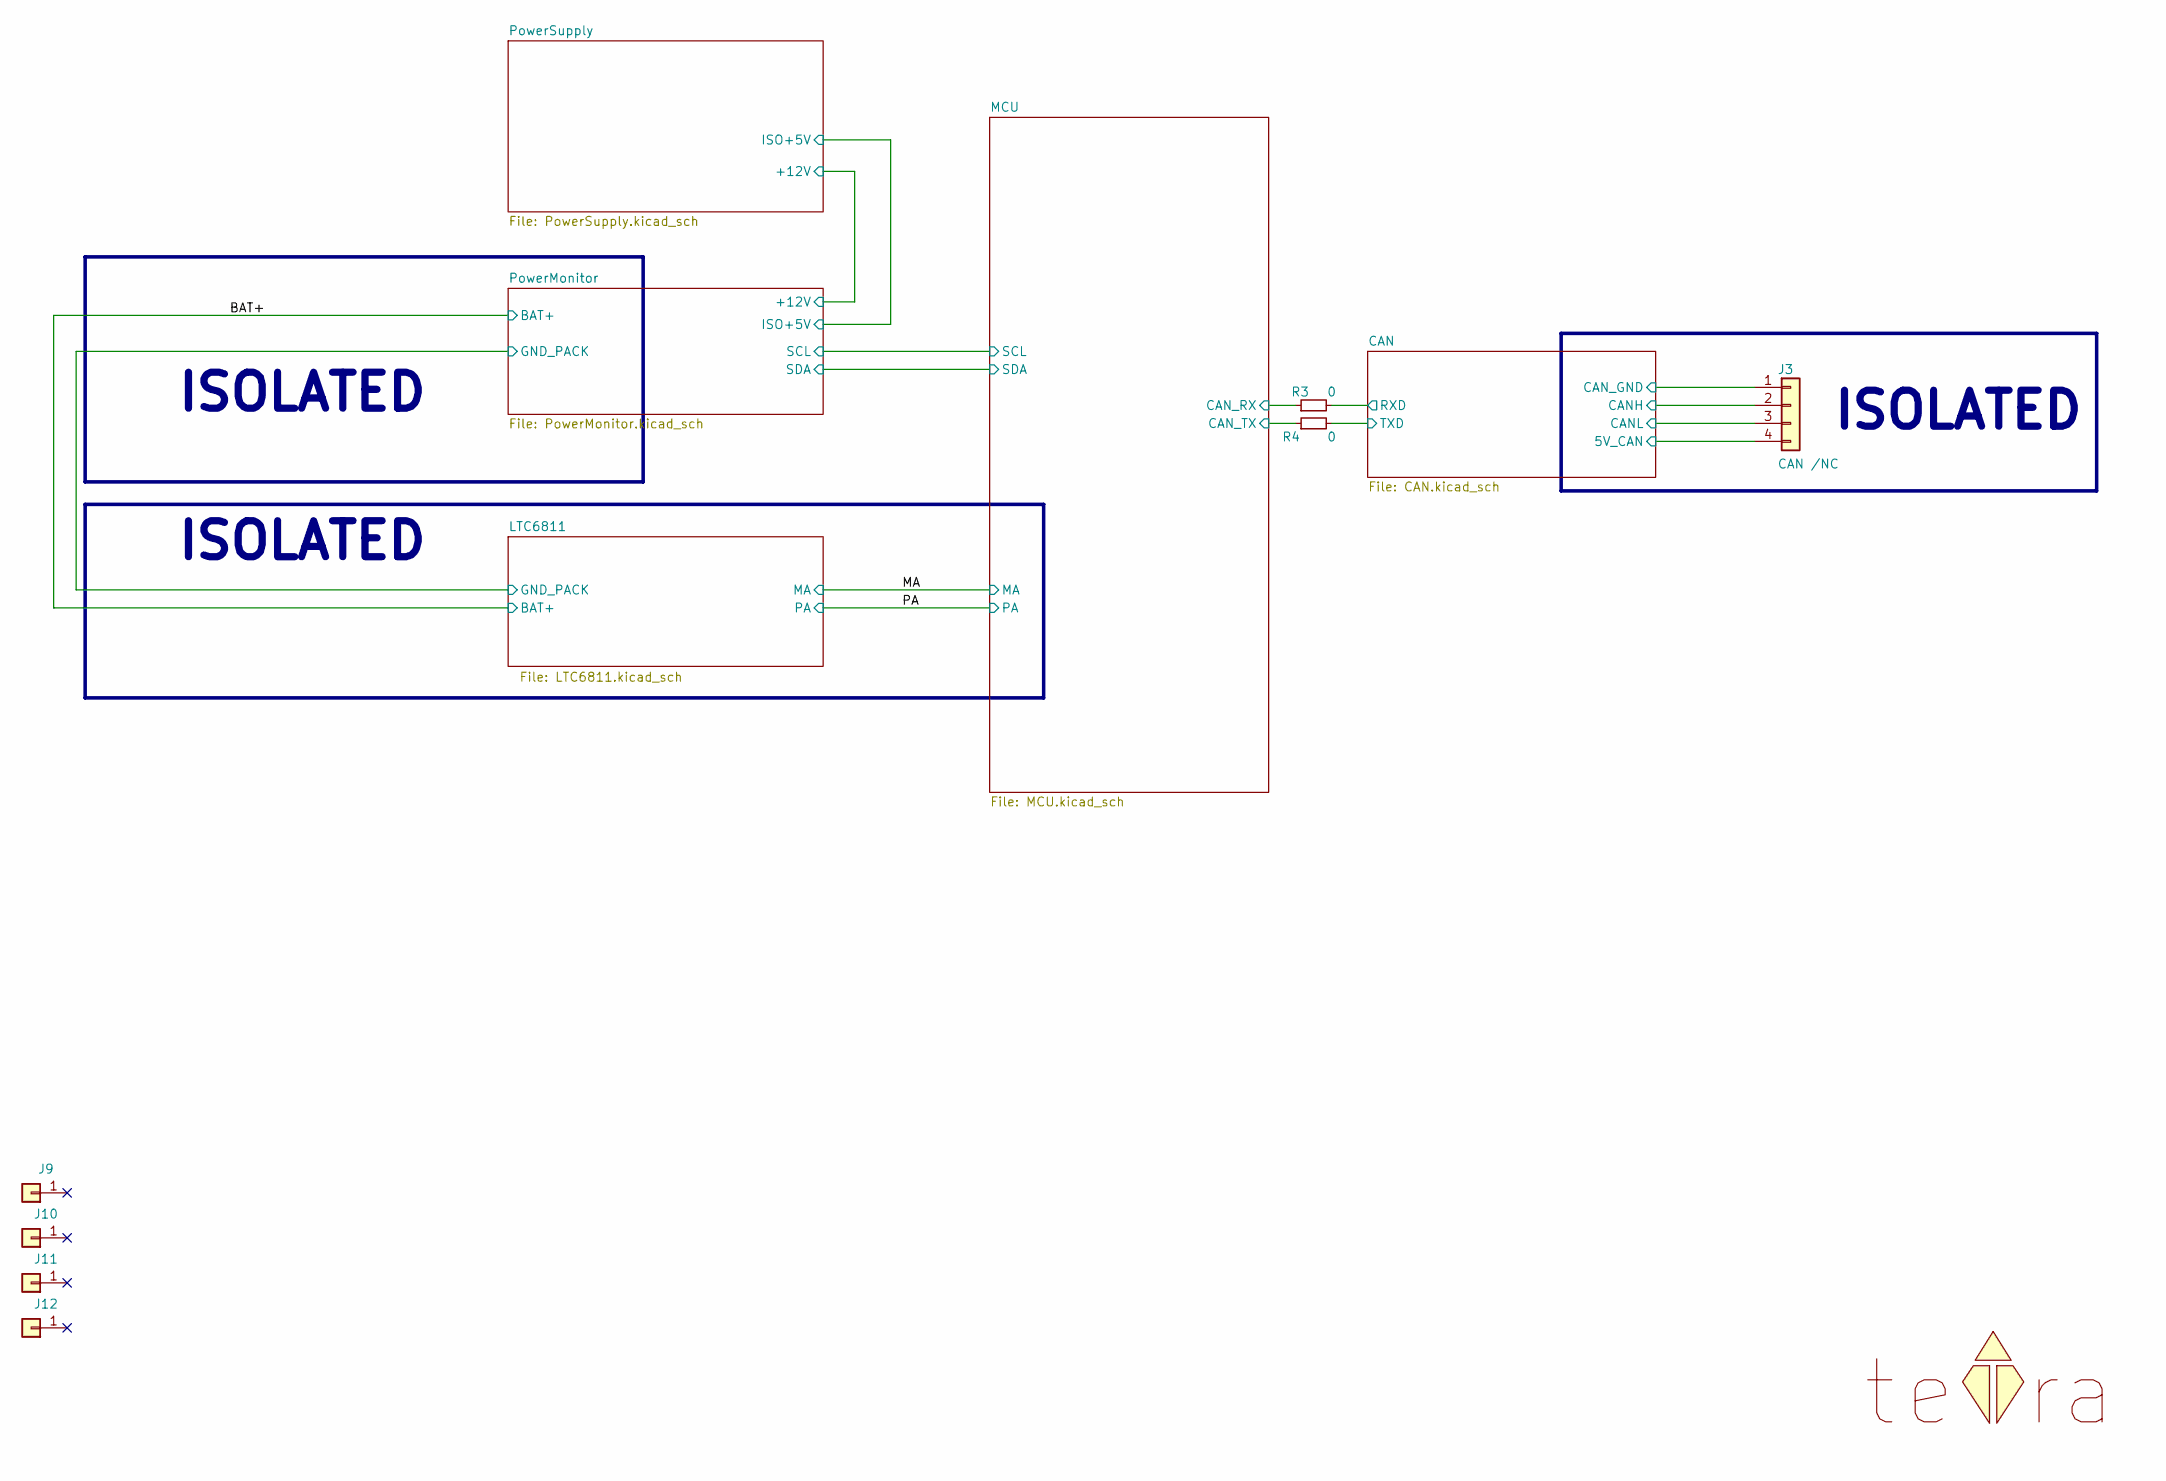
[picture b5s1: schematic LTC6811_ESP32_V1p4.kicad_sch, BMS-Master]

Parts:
J3: CAN /NC; PinHeader_1x04_P2.54mm_Vertical; MPN G800W304018EU
J9, J10, J11, J12: Hole /NC; MountingHole_3.2mm_M3_ISO7380_Pad; MPN N/A
LOGO1: teTra /NC; teTra-LOGO
R3, R4: 0; R_0603_1608Metric; MPN RC0603JR-070RL

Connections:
/CAN/5V_CAN: J3.4; also elsewhere on the board
/CAN/CANH: J3.2; also elsewhere on the board
/CAN/CANL: J3.3; also elsewhere on the board
/CAN/CAN_GND: J3.1; also elsewhere on the board
/CAN/RXD: R3.2; also elsewhere on the board
/CAN/TXD: R4.2; also elsewhere on the board
/CAN_RX: R3.1
/CAN_TX: R4.1

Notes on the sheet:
ISOLATED

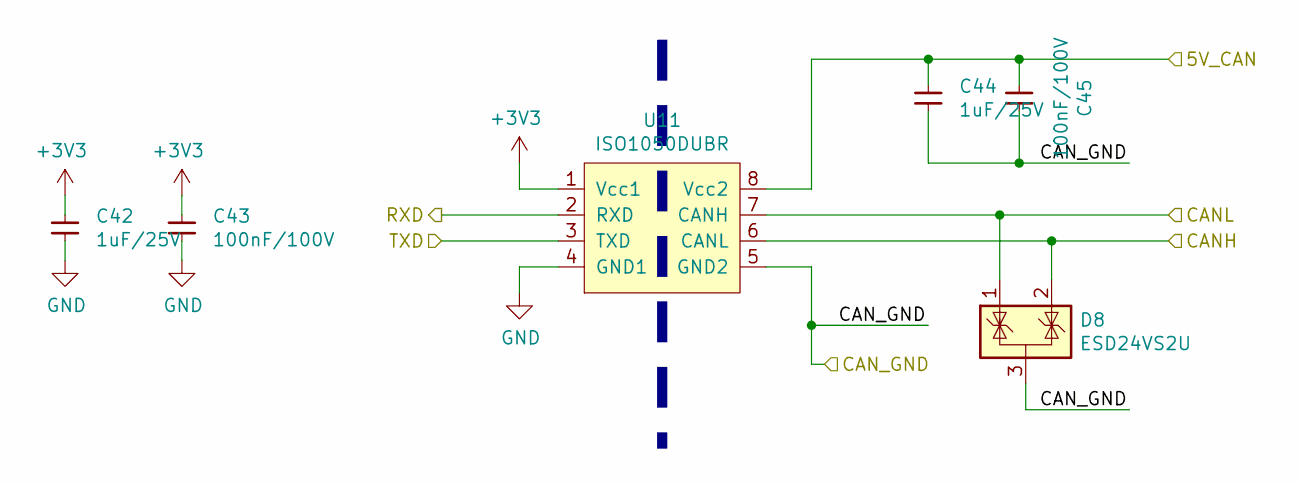
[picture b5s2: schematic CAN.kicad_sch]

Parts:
C42, C44: 1uF/25V; C_0603_1608Metric; MPN 0603B105K250XD
C43, C45: 100nF/100V; C_0603_1608Metric; MPN CL10B104KC8NNNC
D8: ESD24VS2U; SOT-23; MPN ESD24VS2UE6327HTSA1
U11: ISO1050DUBR; SOP-8_6.62x9.15mm_P2.54mm; MPN ISO1050DUBR

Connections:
/CAN/5V_CAN: C44.1, C45.2, U11.8 (Vcc2); also elsewhere on the board
/CAN/CANH: D8.2 (K), U11.6 (CANL); also elsewhere on the board
/CAN/CANL: D8.1 (K), U11.7 (CANH); also elsewhere on the board
/CAN/CAN_GND: C44.2, C45.1, D8.3 (A), U11.5 (GND2); also elsewhere on the board
/CAN/RXD: U11.2 (RXD); also elsewhere on the board
/CAN/TXD: U11.3 (TXD); also elsewhere on the board
